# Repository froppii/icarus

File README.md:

# icarus
a retro vhs player themed mp3 player, complete with tactile switches and a fun volume button

## why?
ive always wanted a dedicated mp3 player so i can listen to music separately without draining my phone battery too quickly, aswell as not having to use spotify. im also learning more on how to make pcbs and 3d model case from this!

## parts and features
**parts**:
- mcu: esp32 s3 wroom 1
- dac: TAD5212IRGER
- display: ili9431
- power: 3.7V 2000mAh lipo battery
- pcb: 4 layers

**features**:
- 3.5mm headphone jack
- 2.8 inch display
- full sized sd card + 1-bit sdmmc audio streaming
- 5 tactile switches and a rotary encoder
- bluetooth 5.0
- programmable eq

## PCB
4 layer pcb

## case
the case is still WIP! but i made a cad to show the general gist of how it would look like

## firmware
firmware coming soon

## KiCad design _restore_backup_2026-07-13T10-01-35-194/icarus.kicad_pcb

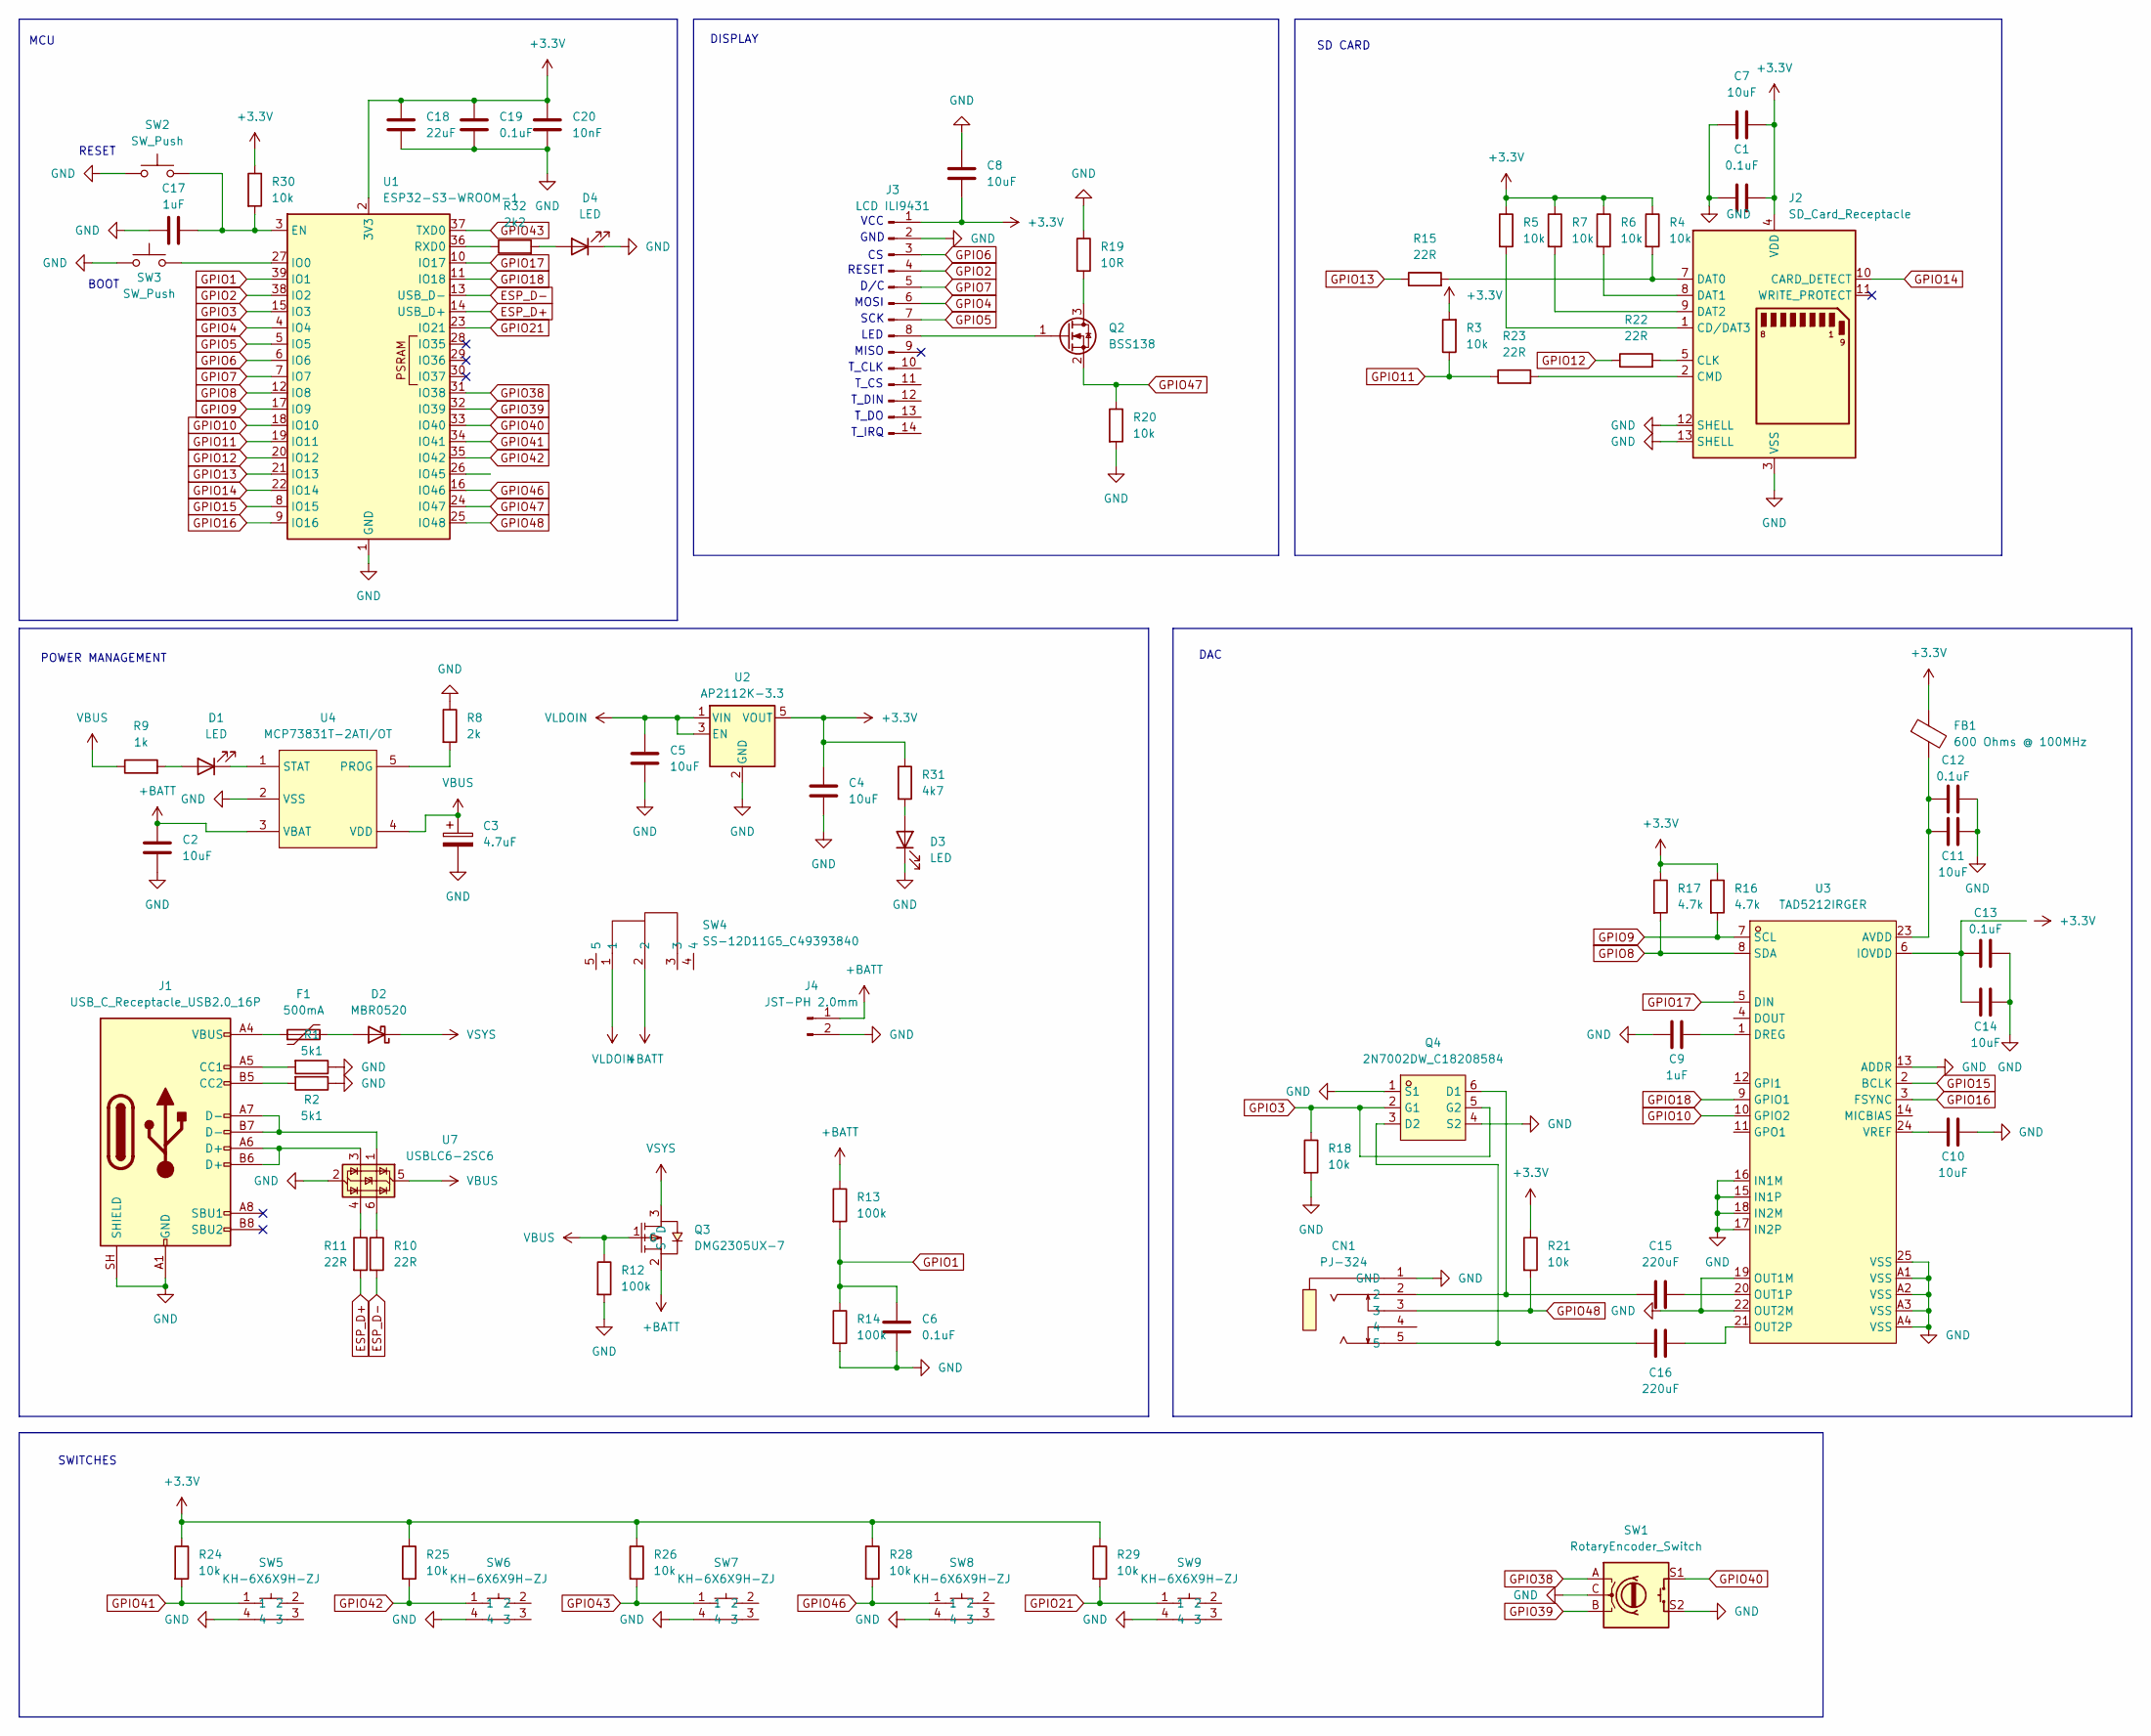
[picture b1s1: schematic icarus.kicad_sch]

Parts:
C1, C6, C12, C13, C19: 0.1uF; C_0603_1608Metric_Pad1.08x0.95mm_HandSolder
C2, C4, C5, C7, C8, C10, C11, C14: 10uF; C_0603_1608Metric_Pad1.08x0.95mm_HandSolder
C3: 4.7uF; C_0603_1608Metric_Pad1.08x0.95mm_HandSolder
C9, C17: 1uF; C_0603_1608Metric_Pad1.08x0.95mm_HandSolder
C15, C16: 220uF; CP_EIA-7343-43_Kemet-X_HandSolder
C18: 22uF; C_0603_1608Metric_Pad1.08x0.95mm_HandSolder
C20: 10nF; C_0603_1608Metric_Pad1.08x0.95mm_HandSolder
CN1: PJ-324; AUDIO-TH_PJ-324-M; MPN PJ-324; LCSC Part C22355738
D1, D3, D4: LED; LED_0603_1608Metric_Pad1.05x0.95mm_HandSolder
D2: MBR0520; D_SOD-123
F1: 500mA; Fuse_1812_4532Metric_Pad1.30x3.40mm_HandSolder
FB1: 600 Ohms @ 100MHz; R_0805_2012Metric_Pad1.20x1.40mm_HandSolder
J1: USB_C_Receptacle_USB2.0_16P; USB_C_Receptacle_GCT_USB4105-xx-A_16P_TopMnt_Horizontal
J2: SD_Card_Receptacle; SD-SMD_SD-006S-T
J3: LCD ILI9431; PinHeader_1x14_P2.54mm_Vertical
J4: JST-PH 2.0mm; JST_PH_S2B-PH-K_1x02_P2.00mm_Horizontal
Q2: BSS138; SOT-23
Q3: DMG2305UX-7; SOT-23-3_L2.9-W1.3-P1.90-LS2.4-BR; MPN DMG2305UX-7; LCSC Part C150470
Q4: 2N7002DW_C18208584; SOT-363_L2.1-W1.3-P0.65-LS2.3-BL; MPN 2N7002DW; LCSC Part C18208584
R1, R2: 5k1; R_0603_1608Metric_Pad0.98x0.95mm_HandSolder
R3, R4, R5, R6, R7, R18, R20, R21, R24, R25, R26, R28, R29, R30: 10k; R_0603_1608Metric_Pad0.98x0.95mm_HandSolder
R8: 2k; R_0603_1608Metric_Pad0.98x0.95mm_HandSolder
R9: 1k; R_0603_1608Metric_Pad0.98x0.95mm_HandSolder
R10, R11, R15, R22, R23: 22R; R_0603_1608Metric_Pad0.98x0.95mm_HandSolder
R12, R13, R14: 100k; R_0603_1608Metric_Pad0.98x0.95mm_HandSolder
R16, R17: 4.7k; R_0603_1608Metric_Pad0.98x0.95mm_HandSolder
R19: 10R; R_0603_1608Metric_Pad0.98x0.95mm_HandSolder
R31: 4k7; R_0603_1608Metric_Pad0.98x0.95mm_HandSolder
R32: 2k2; R_0603_1608Metric_Pad0.98x0.95mm_HandSolder
SW1: RotaryEncoder_Switch; RotaryEncoder_Alps_EC12E-Switch_Vertical_H20mm
SW2, SW3: SW_Push; SW_PUSH_6mm
SW4: SS-12D11G5_C49393840; SW-TH_SS-12D11G5; MPN SS-12D11G5; LCSC Part C49393840
SW5, SW6, SW7, SW8, SW9: KH-6X6X9H-ZJ; SW-TH_KH-6X6X9H-ZJ; MPN KH-6X6X9H-ZJ; LCSC Part C2837545
U1: ESP32-S3-WROOM-1
U2: AP2112K-3.3; SOT-23-5
U3: TAD5212IRGER; VQFN-24_L4.0-W4.0-P0.50-BL-EP2.1_1; MPN TAD5212IRGER; LCSC Part C45068920
U4: MCP73831T-2ATI/OT; SOT-23-5_L3.0-W1.7-P0.95-LS2.8-BR; MPN MCP73831T-2ATI/OT; LCSC Part C14879
U7: USBLC6-2SC6; SOT-23-6

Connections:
+3.3V: C1.2, C4.1, C7.1, C8.2, C18.1, C19.1, C20.1, FB1.1, J2.4 (VDD), J3.1, R3.2, R4.1, R5.1, R6.1, R7.1, R16.1, R17.1, R21.1, R24.1, R25.1, R26.1, R28.1, R29.1, R30.1, R31.1, U1.2 (3V3), U2.5 (VOUT)
+BATT: C2.1, J4.1, Q3.2 (S), R13.1, SW4.2, U4.3 (VBAT)
ESP_D+: R11.2, U1.14 (USB_D+)
ESP_D-: R10.2, U1.13 (USB_D-)
GND: C1.1, C2.2, C3.2, C4.2, C5.2, C6.2, C7.2, C8.1, C9.1, C10.2, C11.1, C12.1, C13.1, C14.2, C17.1, C18.2, C19.2, C20.2, CN1.1 (GND), D3.1 (K), D4.1 (K), J1.A1 (GND), J1.A12 (GND), J1.B1 (GND), J1.B12 (GND), J1.SH (SHIELD), J2.3 (VSS), J2.6 (VSS), J2.12 (SHELL), J2.13 (SHELL), J3.2, J4.2, Q4.1 (S1), Q4.4 (S2), R1.1, R2.1, R8.1, R12.2, R14.2, R18.2, R19.1, R20.2, SW1.C, SW1.S2, SW2.1, SW3.1, SW5.4, SW6.4, SW7.4, SW8.4, SW9.4, U1.1 (GND), U1.40 (GND), U1.41 (GND), U2.2 (GND), U3.13 (ADDR), U3.15 (IN1P), U3.16 (IN1M), U3.17 (IN2P), U3.18 (IN2M), U3.19 (OUT1M), U3.22 (OUT2M), U3.25 (VSS), U3.A1 (VSS), U3.A2 (VSS), U3.A3 (VSS), U3.A4 (VSS), U4.2 (VSS), U7.2 (GND)
GPIO1: C6.1, R13.2, R14.1, U1.39 (IO1)
GPIO2: J3.4, U1.38 (IO2)
GPIO3: Q4.2 (G1), Q4.5 (G2), R18.1, U1.15 (IO3)
GPIO4: J3.6, U1.4 (IO4)
GPIO5: J3.7, U1.5 (IO5)
GPIO6: J3.3, U1.6 (IO6)
GPIO7: J3.5, U1.7 (IO7)
GPIO8: R17.2, U1.12 (IO8), U3.8 (SDA)
GPIO9: R16.2, U1.17 (IO9), U3.7 (SCL)
GPIO10: U1.18 (IO10), U3.10 (GPIO2)
GPIO11: R3.1, R23.1, U1.19 (IO11)
GPIO12: R22.1, U1.20 (IO12)
GPIO13: R15.1, U1.21 (IO13)
GPIO14: J2.10 (CARD_DETECT), U1.22 (IO14)
GPIO15: U1.8 (IO15), U3.2 (BCLK)
GPIO16: U1.9 (IO16), U3.3 (FSYNC)
GPIO17: U1.10 (IO17), U3.5 (DIN)
GPIO18: U1.11 (IO18), U3.9 (GPIO1)
GPIO21: R29.2, SW9.1, U1.23 (IO21)
GPIO38: SW1.A, U1.31 (IO38)
GPIO39: SW1.B, U1.32 (IO39)
GPIO40: SW1.S1, U1.33 (IO40)
GPIO41: R24.2, SW5.1, U1.34 (IO41)
GPIO42: R25.2, SW6.1, U1.35 (IO42)
GPIO43: R26.2, SW7.1, U1.37 (TXD0)
GPIO46: R28.2, SW8.1, U1.16 (IO46)
GPIO47: Q2.2 (S), R20.1, U1.24 (IO47)
GPIO48: CN1.3, R21.2, U1.25 (IO48)
unnamed: D1.2 (A), R9.2
unnamed: D1.1 (K), U4.1 (STAT)
unnamed: D2.2 (A), F1.2
unnamed: D3.2 (A), R31.2
unnamed: D4.2 (A), R32.2
unnamed: F1.1, J1.A4 (VBUS), J1.A9 (VBUS), J1.B4 (VBUS), J1.B9 (VBUS)
unnamed: J1.A5 (CC1), R1.2
unnamed: J1.B5 (CC2), R2.2
unnamed: J1.A6 (D+), J1.B6 (D+), U7.3 (I/O2)
unnamed: J1.A7 (D-), J1.B7 (D-), U7.1 (I/O1)
unnamed: J2.1 (CD/DAT3), R5.2
unnamed: J2.5 (CLK), R22.2
unnamed: J2.2 (CMD), R23.2
unnamed: J2.7 (DAT0), R4.2, R15.2
unnamed: J2.8 (DAT1), R6.2
unnamed: J2.9 (DAT2), R7.2
unnamed: J3.8, Q2.1 (G)
unnamed: Q2.3 (D), R19.2
unnamed: C15.2, CN1.2, Q4.6 (D1)
unnamed: C16.1, CN1.5, Q4.3 (D2)
unnamed: R10.1, U7.6 (I/O1)
unnamed: R11.1, U7.4 (I/O2)
unnamed: C17.2, R30.2, SW2.2, U1.3 (EN)
unnamed: SW3.2, U1.27 (IO0)
unnamed: R32.1, U1.36 (RXD0)
unnamed: C11.2, C12.2, FB1.2, U3.23 (AVDD)
unnamed: C9.2, U3.1 (DREG)
unnamed: C13.2, C14.1, U3.6 (IOVDD)
unnamed: C15.1, U3.20 (OUT1P)
unnamed: C16.2, U3.21 (OUT2P)
unnamed: C10.1, U3.24 (VREF)
unnamed: R8.2, U4.5 (PROG)
VBUS: C3.1, Q3.1 (G), R9.1, R12.1, U4.4 (VDD), U7.5 (VBUS)
VLDOIN: C5.1, SW4.1, U2.1 (VIN), U2.3 (EN)
VSYS: D2.1 (K), Q3.3 (D)

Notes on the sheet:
SD CARD
T_DIN
RESET
T_IRQ
BOOT
SWITCHES
DAC
MOSI
T_CLK
SCK
LED
D/C
T_DO
MCU
MISO
POWER MANAGEMENT
T_CS
VCC
GND
RESET
DISPLAY

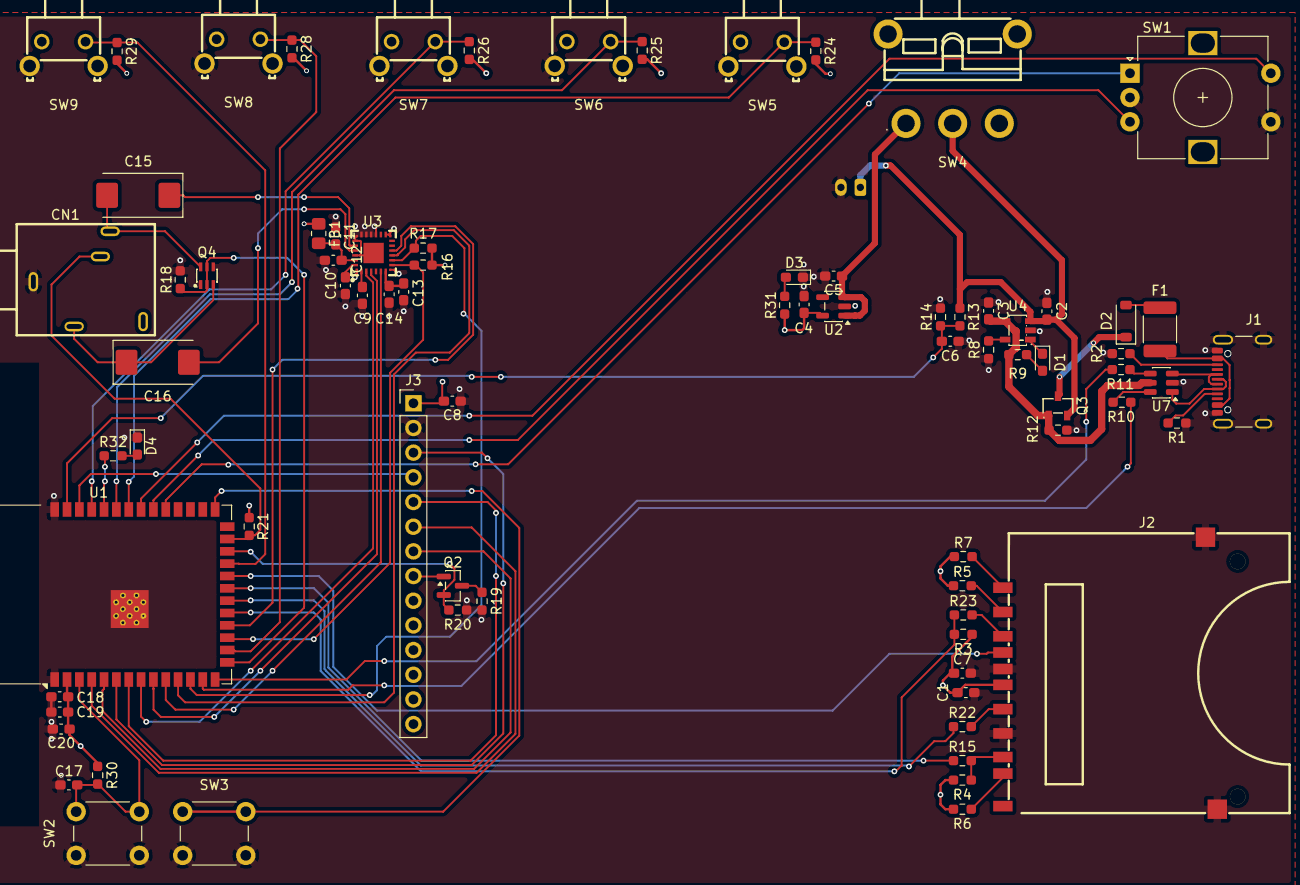
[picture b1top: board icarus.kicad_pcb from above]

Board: 4 copper layers, 79 parts (1 on the bottom side), 68 nets.
